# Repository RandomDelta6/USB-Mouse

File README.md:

# Introduction
This is a basic USB mouse PCB based on the PAW3526D8-FJY2 Sensor in 8P SDIP 10x12.5 mm Package. It features 800 dpi resolution. The PCB is designed to be extremely cost efficient and resilient to dust interference. It features less than 80mA Active power draw and less than 10mA Idle draw. It uses an optical rotary encoder for accurate scroll count with <0.3% error rate. It uses USB 2.0 interface and complies with USB power Suspend Feature. The high tracking frequency allows it to measure even fast swipes accurately with less than 2% creepage even under suboptimal tracking conditions. 

Sensor Pixel Dump of pictures on different surfaces:  

TLDR: A basic USB mouse with left, right and middle click with a scroll wheel with enough performance and reliability to be used as a daily driver for office work. It has a fixed native dpi of 800 and no fancy edpi or dpi switching capabilities. Firmware is integrated in the PAW3526D8-FJY2 sensor and comes preflashed on the chip.

# Optical Sensor
The Optical Sensor Chosen for this PCB is PAW3526D8-FJY2, which is an MCU cum Sensor unit. It offers a small footprint and simple pinout for easy configuration and a space efficient and cost effective board layout.
## Description
PAW3526D8-FJY2 is based on optical navigation technology, which measures changes in position by optically acquiring sequential surface images (frames) and mathematically determining the direction and magnitude of movement. The sensor is housed in an 8-pin staggered dual inline package (DIP). It is designed for use with the M1 OptilensBis 02  03 Focussing Lens and the 003091-0000 SZ260 LED Clip, providing an optical mouse solution that is compact and affordable. There are no moving
parts, so precision optical alignment is not required, thereby facilitating high volume assembly.

## Theory of Operation
The PAW3526D8-FJY2 is based on Optical Navigation Technology. It contains an Image Acquisition System (IAS), a Digital Signal Processor (DSP). The IAS acquires microscopic surface images via the lens and illumination system. These images are processed by the DSP to determine the direction and distance of motion

## Features
• Precise optical navigation technology  
• Small form factor (10 mm x 12.5 mm footprint)  
• No mechanical moving parts   
• Complete 2D motion sensor  
• USB interface for simple design  
• Smooth surface navigation  
• Frame speed up to 3000 fps 
• Accurate motion up to 12 ips  
• 800 dpi resolution  
• High reliability   
• High speed motion detector   
• Wave solderable   
• Single 5.0 volt power supply  
• <50mA Active power draw
• <5mA Idle power draw
• Conforms to USB suspend mode specifications  
• Power conservation mode during times of no movement   
• 8-pin staggered dual inline package (DIP)  
• -30°C to 80°C Standard Operating Range

Package Specifications:  

# Schematic

# PCB

PCB Copper Trace View

PCB Front View

PCB Back View

# Usage

## PCB Assembly 
1.Wave solder the entire assembly in a no-wash solder process utilizing solder fixture.   
2.Insert the sensor and all other electrical components into PCB. Components marked NC in Component Glossary should be ignored. Note: Pin 1 of the sensor should always be the reference point of mechanical cutouts.    
3.Reflow THT Components which include the illumination LEDs, Optical Rotary Encoder, Switches, Jumpers and PAW3526D8-FJY2 Sensor before reflowing SMD components over hot air.   
## Capacitor Overview
• All capacitor footprints are for 0603 Imperial Footprint   
• The 0.1 uF caps must be ceramic.   
• Caps should have less than 5 nH of self inductance   
• Caps should have less than 0.2 ohms ESR   
• MLCC Surface mount parts are recommended   
## Overview of Optical Mouse Sensor Assembly
The PAW3526D8-FJY2 sensor is designed for mounting on a through hole PCB, looking down. There is an aperture stop and features on the package that align to the lens. M1 OptilensBis 02  03 Focussing Lens provides optics for the imaging of the surface as well as illumination of the surface at the
optimum angle. Features on the lens align it to the sensor, base plate, and clip with the LED. The lens also has a large round flange to provide a long creepage path for any ESD events that occur at the opening of the base plate. The 003091-0000 SZ260 clip holds the LED in relation to the lens. The LED’s leads must be formed first before inserting into the clip. Then, both LED and clip is loaded on the PCB. The clip interlocks the sensor to the lens, and through the lens to the alignment features on the base plate. A 940nm IR LED of sufficient brightness should be used for illumination.

## Product Assembly Considerations
Install the LED Clip on the Sensor Illumination LED. Insert the Retention Clip on the Lens into the slot in the LED  Clip and fold up the assembly. Ensure the lens focal point aligns with the sensor aperture. Guide features or adhesive maybe used on the baseplate to enure the lens assembly stays over the sensor aperture at optimum focus. The sensor aperture ring should self-align to the lens. The optical position reference for the PCB is set by the base plate and lens. Note that the PCB motion due to button presses must be minimized to maintain optical alignment. There MUST be a feature in the top case to press down onto the clip to ensure all components are interlocked to the correct vertical height. Note that the lens
material is polycarbonate and therefore, cyanoacrylate based adhesives or other adhesives that may damage the lens should NOT be used.

## Reference Pictures

LED Clip 003091-0000 SZ260

M1 OptilensBis 02  03 Focussing Lens

Scroll Wheel Assembly ( Wheel with 60 evenly spaced slits)

Reference PCB Top (Back)

Reference PCB Bottom (Front)

Reference PCB Bottom with Lens and LED Clip installed (Front)

Reference PCB In Reference Housing with Scroll Wheel Assembly in Place

# Notes

This PCB is based on the Mouton 1D CR PCB by Logitech found in their popular B100 Mice. This PCB is designed to be a drop in replacement with appropriate guide holes and retention feature placements.

This project has been made with Kicad 5.1.10

While exporting for fabrication the back solder mask layer may be ignored to save on manufacturing costs as it serves no purpose. Through holes may also be replaced with npth and pads on front side of pcb only to reduce cost further.

# Regulatory Information
• Passes EN61000-4-4/IEC801-4 EFTB tests when assembled into a mouse with shielded cable.    
• UL flammability level UL94 V-0.    
• Provides sufficient ESD creepage/clearance distance to avoid discharge up to 15 kV.    
• CLASS 1 LED Product   
• Complies with Canada ICES-003, Class B      

# Disclaimer
I do not assume any liability for the materials, information and opinions provided on, or available through, this project. I disclaim any liability for injury, death or damages resulting from the use thereof.

# Licensing
All PCB design files and hardware are released under the [Creative Commons Attribution Share Alike 4.0 license](https://choosealicense.com/licenses/cc-by-sa-4.0/).

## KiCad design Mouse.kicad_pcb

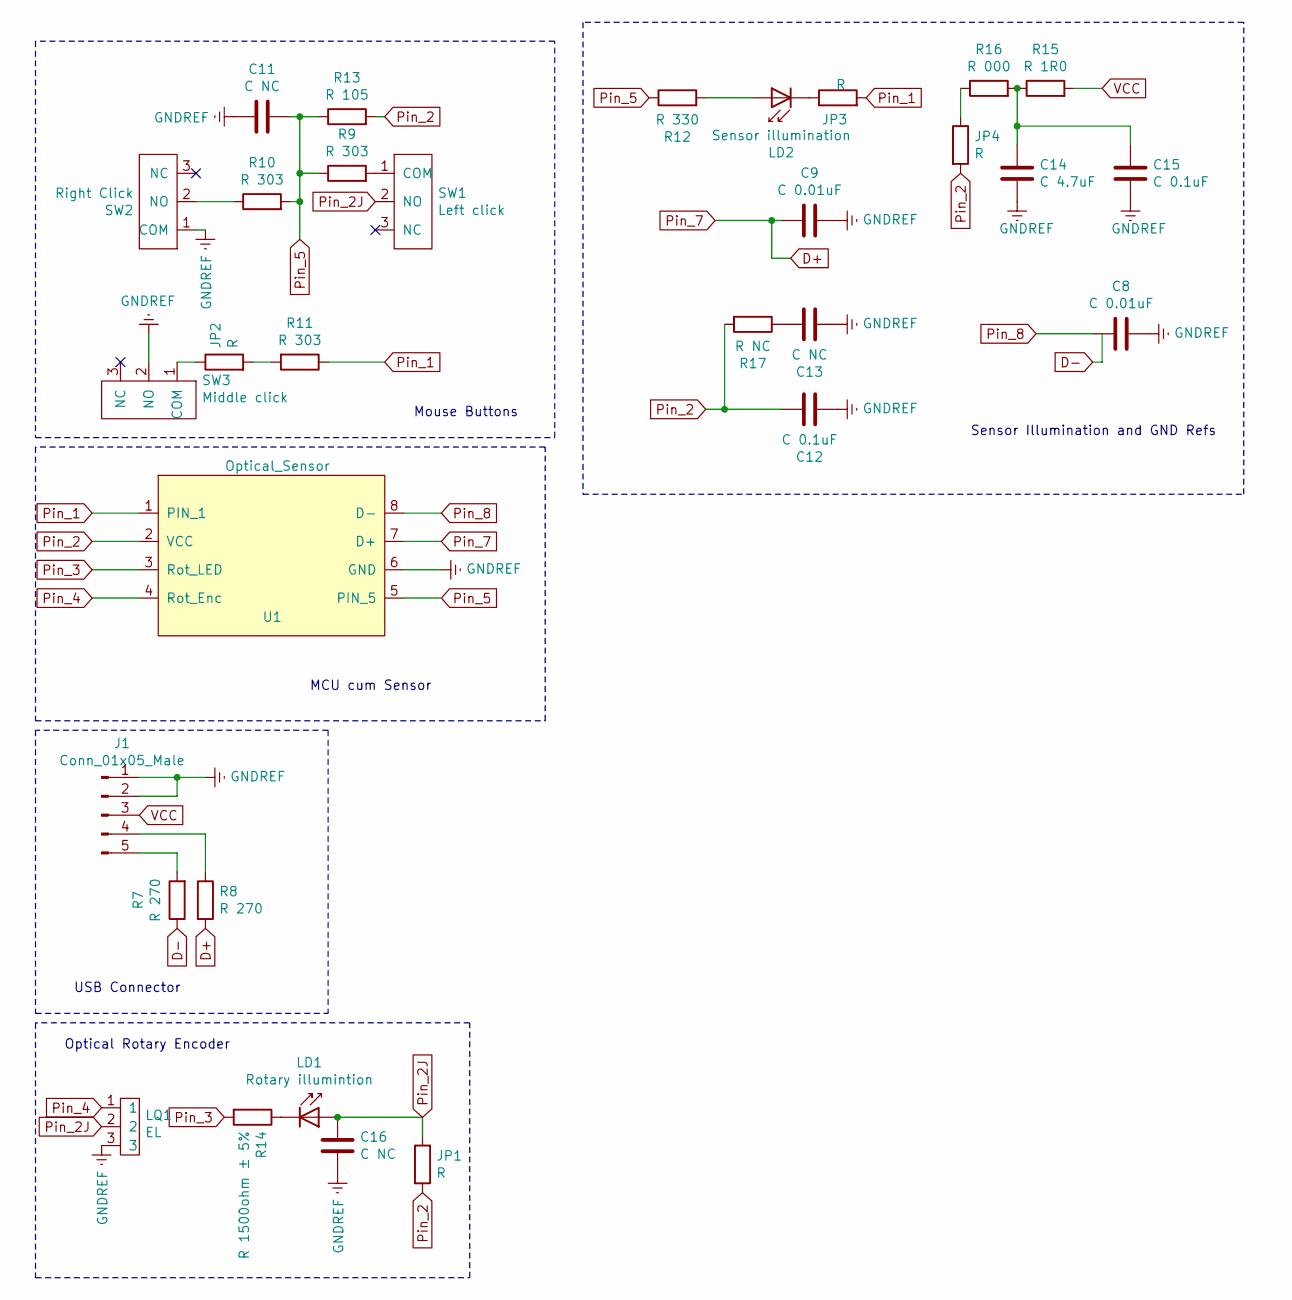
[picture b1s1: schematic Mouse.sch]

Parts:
C8, C9: C 0.01uF; R_0603_1608_Logi
C11, C13, C16: C NC; R_0603_1608_Logi
C12, C15: C 0.1uF; R_0603_1608_Logi
C14: C 4.7uF; R_0603_1608_Logi
J1: Conn_01x05_Male; JST_Conn
JP1, JP2, JP3, JP4: R; JP_Axial_DIN0207_L6.3mm_D2.5mm_P10.16mm_Horizontal
LD1: Rotary illumintion; Rot_LED
LD2: Sensor illumination; LED_Sensor
LQ1: EL; LQ1
R7, R8: R 270; R_0603_1608_Logi
R9, R10, R11: R 303; R_0603_1608_Logi
R12: R 330; R_0603_1608_Logi
R13: R 105; R_0603_1608_Logi
R14: R 1500ohm ± 5%; JP_Axial_DIN0207_L6.3mm_D2.5mm_P10.16mm_Horizontal
R15: R 1R0; R_0603_1608_Logi
R16: R 000; R_0603_1608_Logi
R17: R NC; R_0603_1608_Logi
SW1: Left click; SPDT_Switch
SW2: Right Click; SPDT_Switch
SW3: Middle click; SPDT_Switch
U1: Optical_Sensor; Sensor

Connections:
D+: C9.1, R8.2, U1.7 (D+)
D-: R7.1
GNDREF: C8.2, C9.2, C11.1, C12.1, C13.1, C14.1, C15.2, C16.2, J1.1, J1.2, LQ1.3, SW2.1 (COM), SW3.2 (NO), U1.6 (GND)
unnamed: C13.2, R17.1
unnamed: C14.2, C15.1, R15.1, R16.2
unnamed: J1.4, R8.1
unnamed: J1.5, R7.2
unnamed: JP2.1, SW3.1 (COM)
unnamed: JP2.2, R11.2
unnamed: JP3.1, LD2.1 (K)
unnamed: JP4.1, R16.1
unnamed: LD1.1 (K), R14.1
unnamed: LD2.2 (A), R12.2
unnamed: R9.2, SW1.1 (COM)
unnamed: R10.1, SW2.2 (NO)
Pin_1: JP3.2, R11.1, U1.1 (PIN_1)
Pin_2: C12.2, JP1.2, JP4.2, R13.2, R17.2, U1.2 (VCC)
Pin_2J: C16.1, JP1.1, LD1.2 (A), LQ1.2, SW1.2 (NO)
Pin_3: R14.2, U1.3 (Rot_LED)
Pin_4: LQ1.1, U1.4 (Rot_Enc)
Pin_5: C11.2, R9.1, R10.2, R12.1, R13.1, U1.5 (PIN_5)
Pin_8: C8.1, U1.8 (D-)
VCC: J1.3, R15.2

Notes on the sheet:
Optical Rotary Encoder
USB Connector
MCU cum Sensor
Mouse Buttons
Sensor Illumination and GND Refs

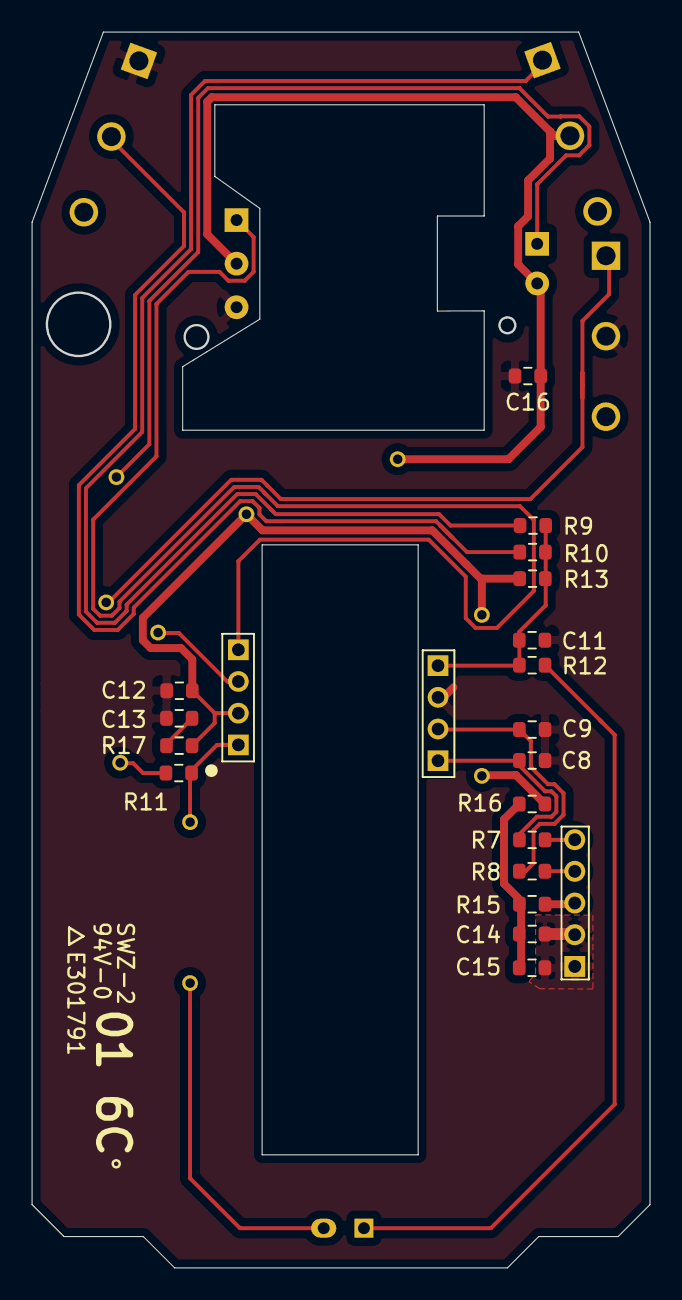
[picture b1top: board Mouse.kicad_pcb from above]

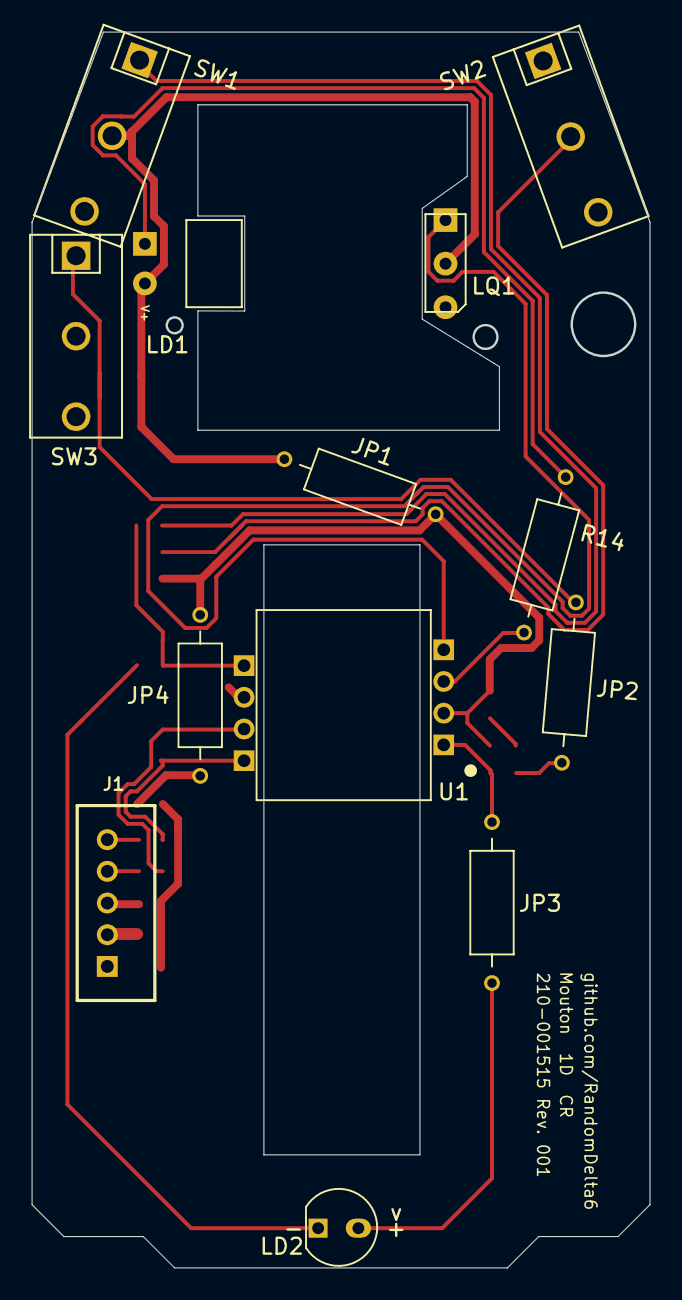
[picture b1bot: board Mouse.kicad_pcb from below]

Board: 2 copper layers, 38.9 x 77.9 mm, 31 parts (13 on the bottom side), 22 nets.

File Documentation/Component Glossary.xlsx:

List of Materials
Sl. No. | Notation | Footprint | Value | Particulars | Remarks
1 | C8 | C_0603 |  | 0.01uF | MLCC
2 | C9 | C_0603 |  | 0.01uF | MLCC
3 | C11 | C_0603 |  |  | NC
4 | C12 | C_0603 |  | 0.1uF | MLCC
5 | C13 | C_0603 |  |  | NC
6 | C14 | C_0603 |  | 4.7uF | MLCC
7 | C15 | C_0603 |  | 0.1uF | MLCC
8 | R7 | R_0603 | R 270
9 | R8 | R_0603 | R 270
10 | R9 | R_0603 | R 303
11 | R10 | R_0603 | R 303
12 | C16 | C_0603 |  |  | NC
13 | R11 | R_0603 | R 303
14 | R12 | R_0603 | R 330
15 | R13 | R_0603 | R 105
16 | R14 | DIN0207 | R 1500ohm ± 5%
17 | R15 | R_0603 | R 1R0
18 | R16 | R_0603 | R 000
19 | R17 | R_0603 |  |  | NC
20 | U1 | 8P SDIP 10x12.5 mm | PAW3526D8-FJY2 | H9165632C | Sensor cum MCU
21 | SW1 | SPDT_SW | 15A 125V | Kailh SF19YA
22 | SW2 | SPDT_SW | 15A 125V | Kailh SF19YA
23 | SW3 | SPDT_SW | 15A 125V | Himake
24 | JP1 | DIN0207 | 0 ohm
25 | JP2 | DIN0207 | 0 ohm
26 | JP3 | DIN0207 | 0 ohm
27 | JP4 | DIN0207 | 0 ohm
28 | LD1 |  |  |  | Optical Rotary Encoder Pair
29 | LD2 |  | 1.4V 100mA | 940 nm IR | Infrared Lamp
30 | LQI |  |  |  | Optical Rotary Encoder Pair
31 | J1 |  |  | JST 2.00MM PITCH 5 PIN

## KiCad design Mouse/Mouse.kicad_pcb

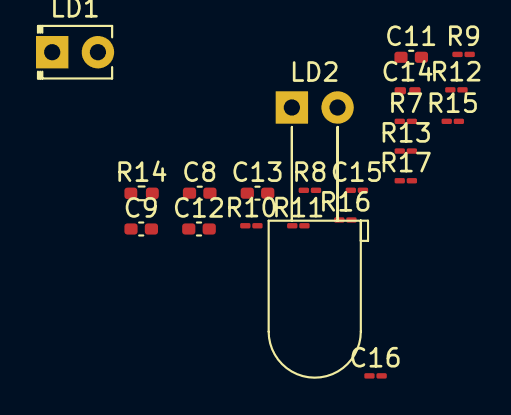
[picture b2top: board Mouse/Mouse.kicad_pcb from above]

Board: 2 copper layers, 21 parts (0 on the bottom side), 9 nets, no tracks yet.

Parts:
C8, C9, C11, C12, C13: C; C_0402_1005Metric_Pad0.74x0.62mm_HandSolder
C14: C; C_0201_0603Metric_Pad0.64x0.40mm_HandSolder
C15: C; C_01005_0402Metric_Pad0.57x0.30mm_HandSolder
C16: C NC; C_01005_0402Metric_Pad0.57x0.30mm_HandSolder
LD1: Rotary illumintion; LED_D2.0mm_W4.0mm_H2.8mm_FlatTop
LD2: Sensor illumination; LED_D5.0mm_Horizontal_O6.35mm_Z15.0mm
R7, R8: R 270; R_01005_0402Metric_Pad0.57x0.30mm_HandSolder
R9, R10: R 303; R_01005_0402Metric_Pad0.57x0.30mm_HandSolder
R11: 330_M_click; R_01005_0402Metric_Pad0.57x0.30mm_HandSolder
R12: 330 LD2 resistor; R_01005_0402Metric_Pad0.57x0.30mm_HandSolder
R13: R 105; R_01005_0402Metric_Pad0.57x0.30mm_HandSolder
R14: R 1500ohm ± 5%; R_0402_1005Metric_Pad0.72x0.64mm_HandSolder
R15: R 1R0; R_01005_0402Metric_Pad0.57x0.30mm_HandSolder
R16: R 000; R_01005_0402Metric_Pad0.57x0.30mm_HandSolder
R17: R; R_01005_0402Metric_Pad0.57x0.30mm_HandSolder

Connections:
D+: C9.1, R8.2
GNDREF: C8.2, C9.2, C11.1, C12.1, C13.1, C14.1, C15.2, C16.2
unnamed: C12.2, R17.1
unnamed: C14.2, C15.1, R15.1, R16.2
unnamed: LD1.1, R14.1
unnamed: LD2.1, R12.2
Pin_1: LD2.2, R11.1
Pin_2: C13.2, C16.1, LD1.2, R13.2, R16.1, R17.2
Pin_5: C11.2, R9.1, R10.2, R12.1, R13.1

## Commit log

2022-08-15 added footprints
2022-08-20 updated footprints
2023-02-08 Updated components
2023-02-09 created the inner and outer edge cuts
2023-02-11 optical sensor marker pushed to 14.5mm approx
2023-02-14 Updated layout
2023-02-15 Updated board layout
2023-02-15 Layout Updated
2023-02-17 Updated Schematics, Layout and Footprints
2023-02-17 Updated Layout and README
2023-02-17 Schematic Correction
2023-02-17 Fixed some copper traces, updated readme snaps
2023-02-17 Update Schematics
